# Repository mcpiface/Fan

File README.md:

# Fan

## Versions

* 1: Simple fan controlled via Raspberry Pi with 1 Wire temperature sensor.
* 2: I2C temperature sensor
* 3: I2C interface to AT Tiny 85 controller for the fan with accelerometer (internal temperature sensor).

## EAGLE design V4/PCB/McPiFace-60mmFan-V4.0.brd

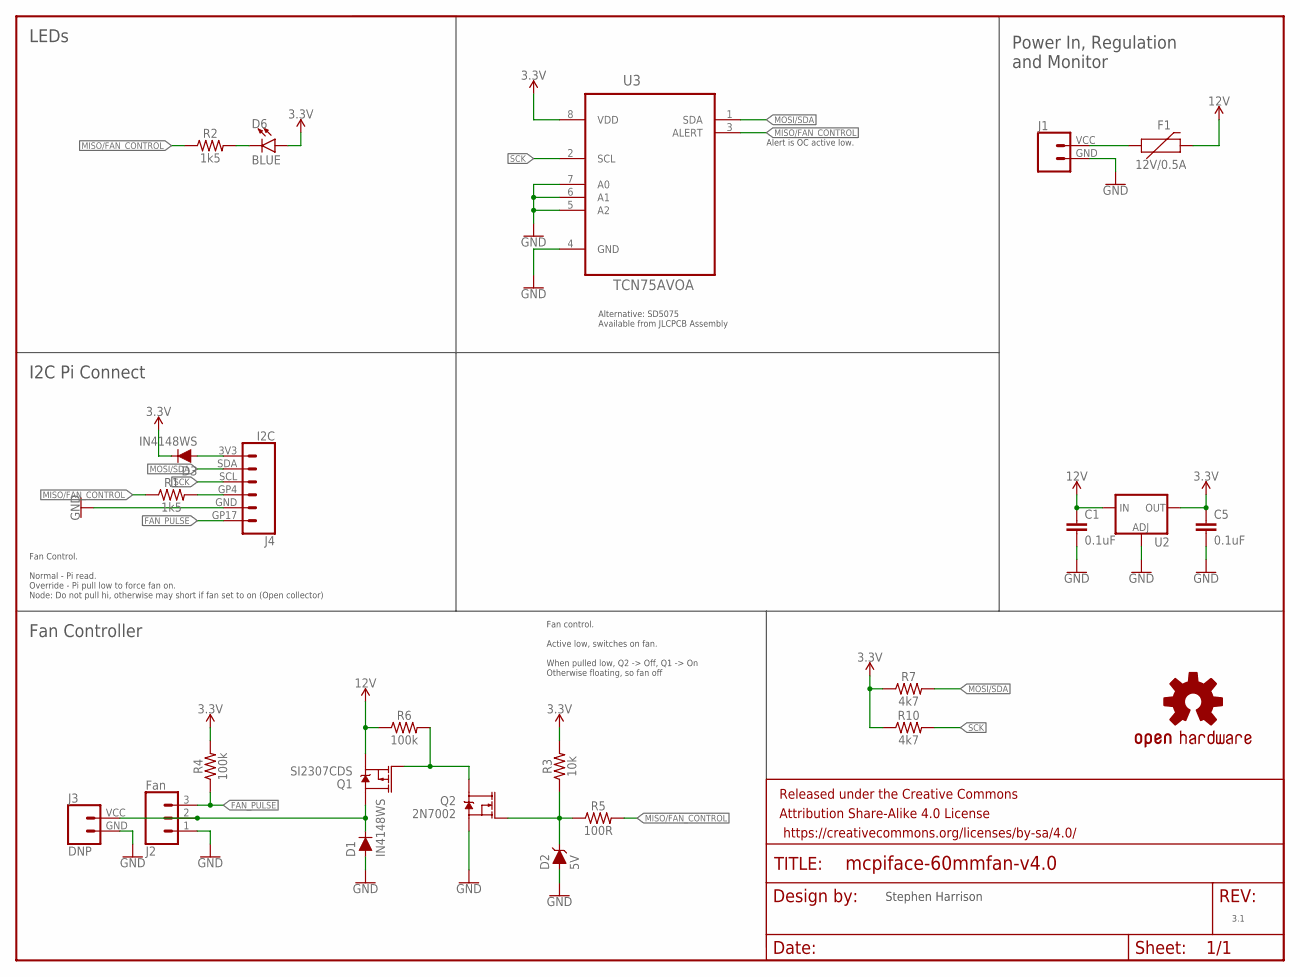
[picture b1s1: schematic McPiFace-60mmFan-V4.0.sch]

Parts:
C1, C5: 0.1uF; 0805
D1, D3: IN4148WS; SOD-323; LCSC C2128
D2: 5V; SOD-323
D6: BLUE; LED-1206
F1: 12V/0.5A; 1206
FRAME1: FRAME-LETTER; CREATIVE_COMMONS
J1: CONN_024UCON-15767; JST-2-SMD-VERT
J2: Fan; JST-3-SMD; FARNELL 9492623
J3: DNP; JST-2-SMD-VERT
J4: I2C; JST-6-SH-1.0MM-TOP
LOGO1: OSHW-LOGOL; OSHW-LOGO-L
Q1: SI2307CDS; SOT23-3; FARNELL 1779262
Q2: 2N7002; SOT23-3; FARNELL 1510761
R1, R2: 1k5; 0805
R3: 10k; 0805
R4, R6: 100k; 0805
R5: 100R; 0805
R7, R10: 4k7; 0805
U2: V_REG_LM1117SOT223; SOT223; LCSC C126027
U3: TCN75AVOA; SOIC127P600X175-8N

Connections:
3.3V: C5.1, D3.C, D6.A, R3.2, R4.2, R7.1, R10.1, U2.2 (OUT), U2.4 (OUT), U3.8 (VDD)
12V: C1.1, F1.2, Q1.2 (S), R6.1, U2.3 (IN)
FAN_PULSE: J2.3 (1), J4.GP17, R4.1
GND: C1.2, C5.2, D1.A, D2.A, J1.GND (1), J2.1 (3), J3.GND (1), J4.GND, Q2.2 (S), U2.1 (ADJ), U3.4 (GND), U3.5 (A2), U3.6 (A1), U3.7 (A0)
MISO/FAN_CONTROL: R1.1, R2.1, R5.2, U3.3 (ALERT)
MOSI/SDA: J4.SDA, R7.2, U3.1 (SDA)
unnamed: D6.C, R2.2
unnamed: J4.GP4, R1.2
unnamed: D3.A, J4.3V3
unnamed: F1.1, J1.VCC (2)
unnamed: D1.C, J2.2, J3.VCC (2), Q1.3 (D)
unnamed: Q1.1 (G), Q2.3 (D), R6.2
unnamed: D2.C, Q2.1 (G), R3.1, R5.1
SCK: J4.SCL, R10.2, U3.2 (SCL)

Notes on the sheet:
3.1
Stephen Harrison
Fan Controller
I2C Pi Connect
Power In, Regulation and Monitor
LEDs
Alert is OC active low.
Fan control. Active low, switches on fan. When pulled low, Q2 -> Off, Q1 -> On Otherwise floating, so fan off
Fan Control. Normal - Pi read. Override - Pi pull low to force fan on. Node: Do not pull hi, otherwise may short if fan set to on (Open collector)
Alternative: SD5075 Available from JLCPCB Assembly

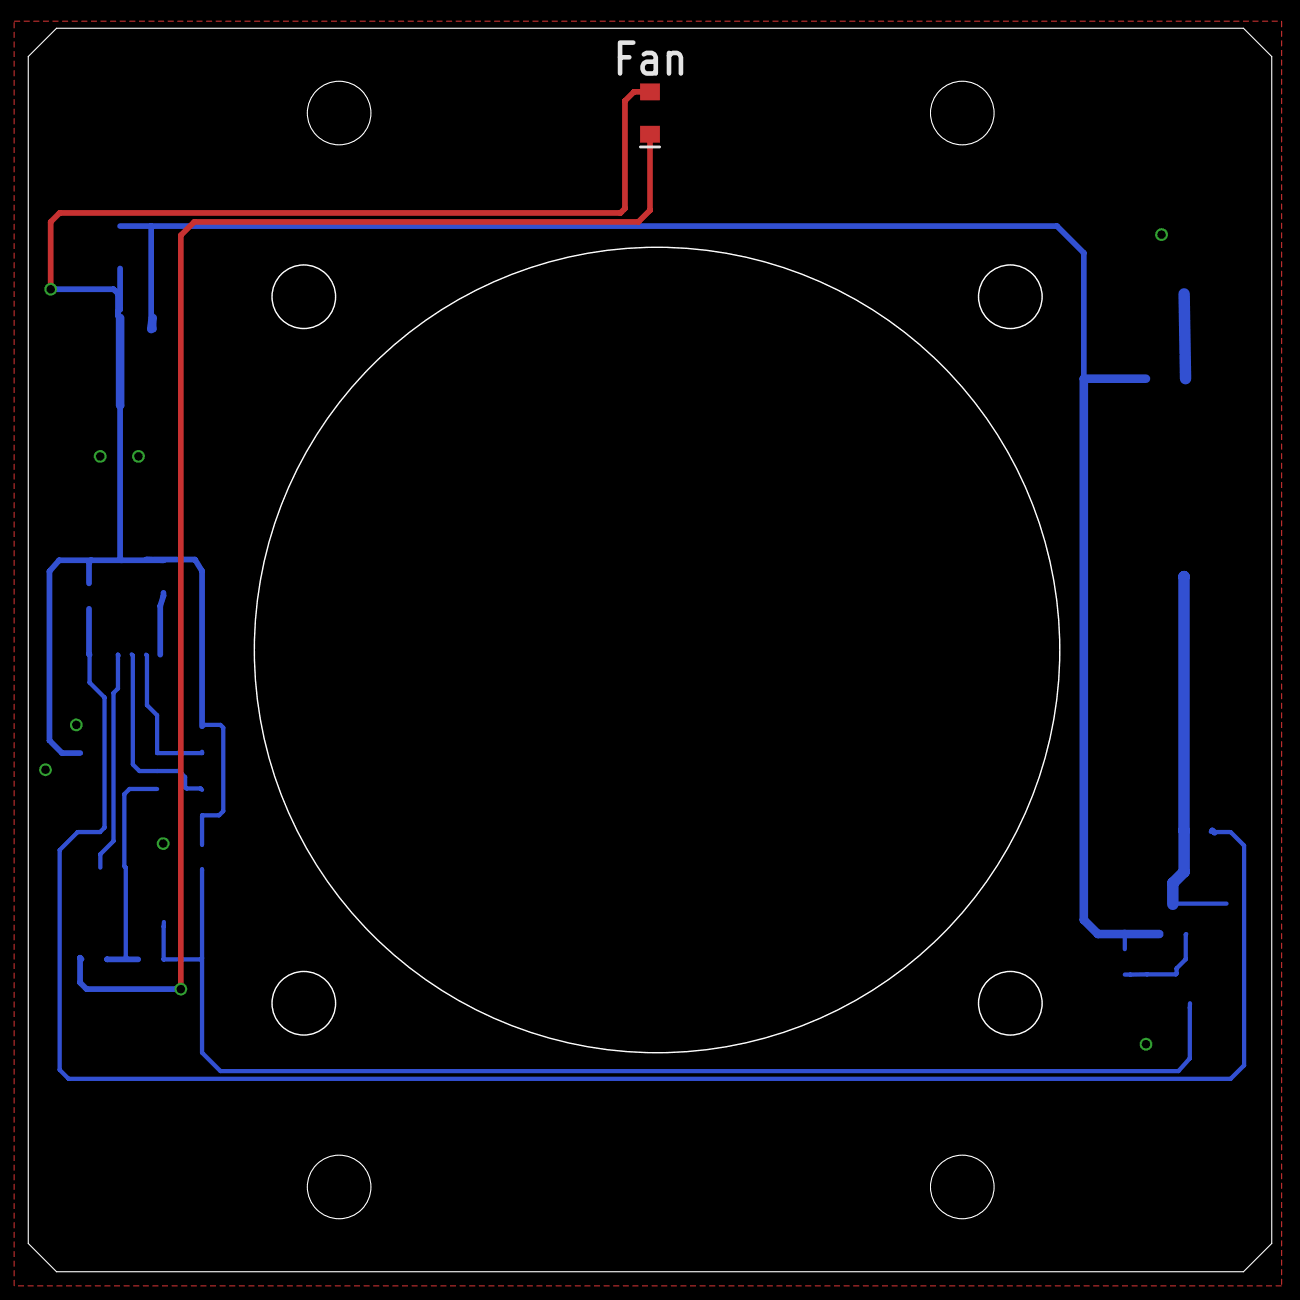
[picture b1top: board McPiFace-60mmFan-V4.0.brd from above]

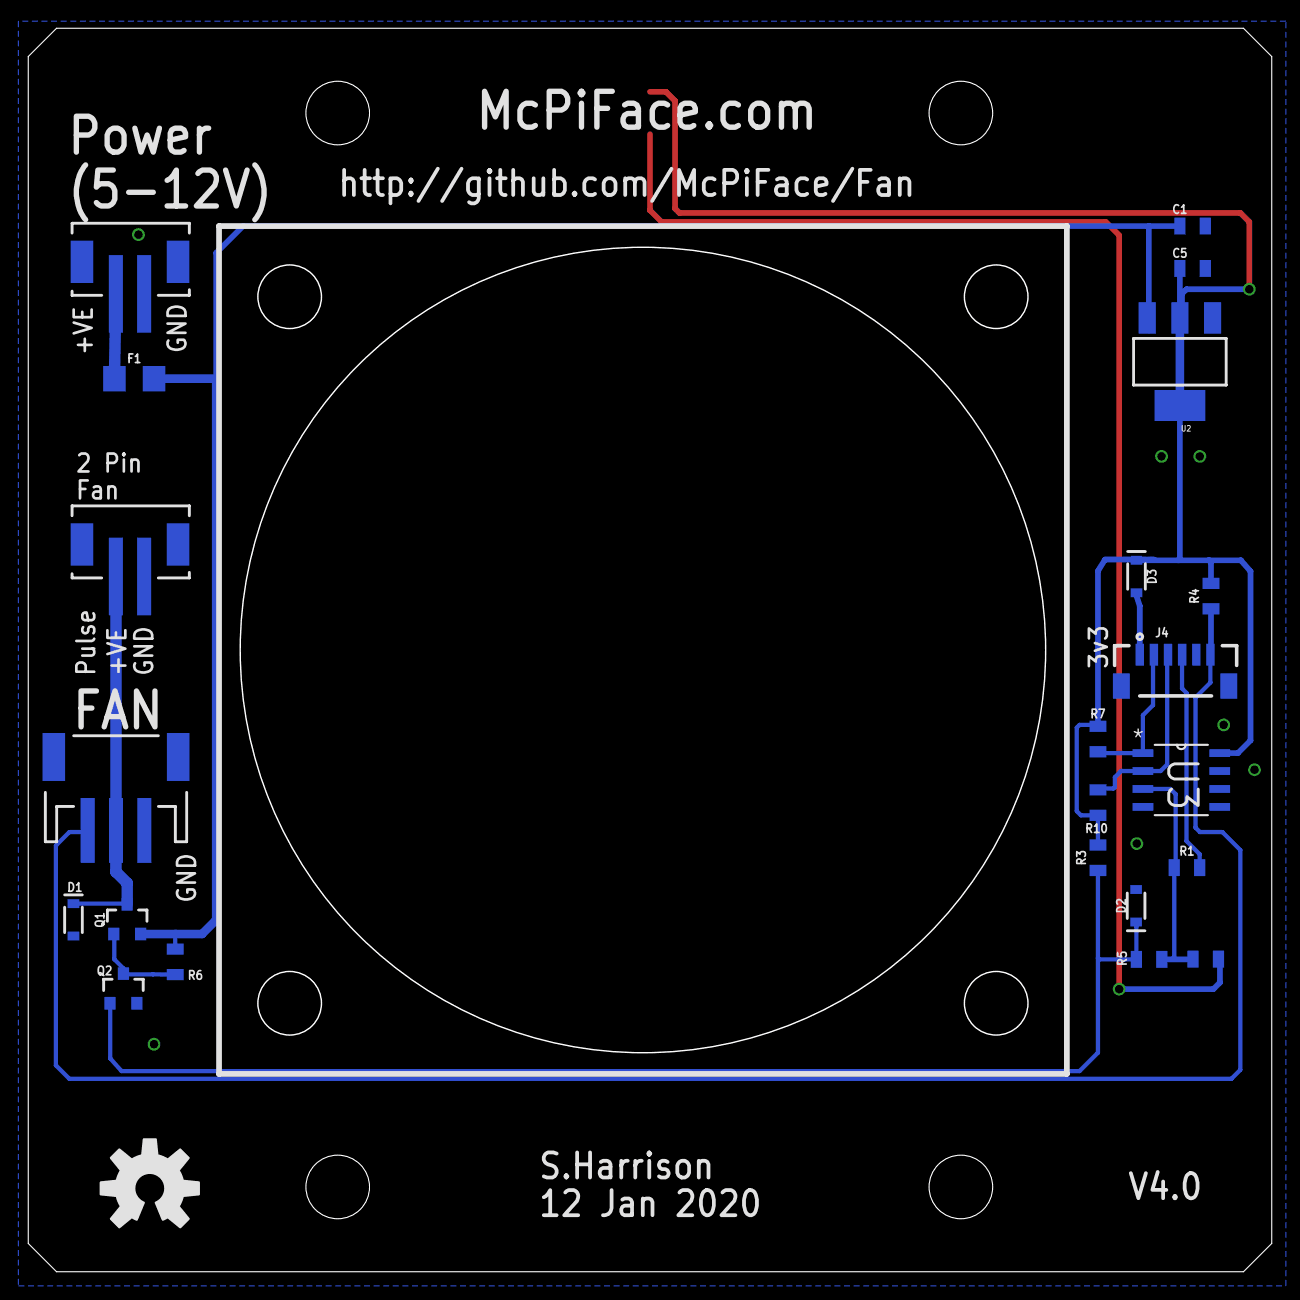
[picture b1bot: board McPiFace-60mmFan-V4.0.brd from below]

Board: 2 copper layers, 87.9 x 87.9 mm, 25 parts (23 on the bottom side), 14 nets.

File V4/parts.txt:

Partlist

Exported from McPiFace-60mmFan-V4.0.brd at 12/01/2020 14:54

EAGLE Version 7.4.0 Copyright (c) 1988-2015 CadSoft

Assembly variant: 

Part     Value          Package            Library               Position (inch)       Orientation

C1       0.1uF          0805               ThingySticks          (0.22047244 2.91338583) MR0
C5       0.1uF          0805               ThingySticks          (0.22047244 2.79527559) MR0
D1       IN4148WS       SOD-323            SparkFun-DiscreteSemi (3.33858268 0.98031496) MR270
D2       5V             SOD-323            SparkFun-DiscreteSemi (0.37795276 1.01968504) MR90
D3       IN4148WS       SOD-323            SparkFun-DiscreteSemi (0.37677165 1.93700787) MR270
D6       BLUE           LED-1206           ThingySticks          (1.73228346 3.22834646) R270
F1       12V/0.5A       1206               SparkFun-Fuses        (3.16929134 2.48818898) MR0
J1                      JST-2-SMD-VERT     SparkFun-Connectors   (3.18110236 2.80314961) MR0
J2       Fan            JST-3-SMD          SparkFun-Connectors   (3.22047244 1.41732283) MR0
J3       DNP            JST-2-SMD-VERT     SparkFun-Connectors   (3.18110236 2.01574803) MR0
J4       I2C            JST-6-SH-1.0MM-TOP McPiFace              (0.26771654 1.66929134) MR0
Q1       SI2307CDS      SOT23-3            SparkFun-DiscreteSemi (3.18897638 0.98031496) MR0
Q2       2N7002         SOT23-3            SparkFun-DiscreteSemi (3.19940945 0.78740157) MR0
R1       1k5            0805               SparkFun-Resistors    (0.23622047 1.12598425) MR0
R2       1k5            0805               SparkFun-Resistors    (0.18385827 0.87086614) MR0
R3       10k            0805               SparkFun-Resistors    (0.48425197 1.15354331) MR90
R4       100k           0805               SparkFun-Resistors    (0.16929134 1.88248031) MR90
R5       100R           0805               SparkFun-Resistors    (0.34173228 0.87027559) MR0
R6       100k           0805               SparkFun-Resistors    (3.05511811 0.86338583) MR270
R7       4k7            0805               SparkFun-Resistors    (0.48425197 1.48425197) MR270
R10      4k7            0805               SparkFun-Resistors    (0.48425197 1.30708661) MR90
U2                      SOT223             SparkFun-IC-Power     (0.25590551 2.53543307) MR180
U3       TCN75AVOA      SOIC127P600X175-8N Microchip-TCN75AVOA   (0.2519685 1.37007874) MR0

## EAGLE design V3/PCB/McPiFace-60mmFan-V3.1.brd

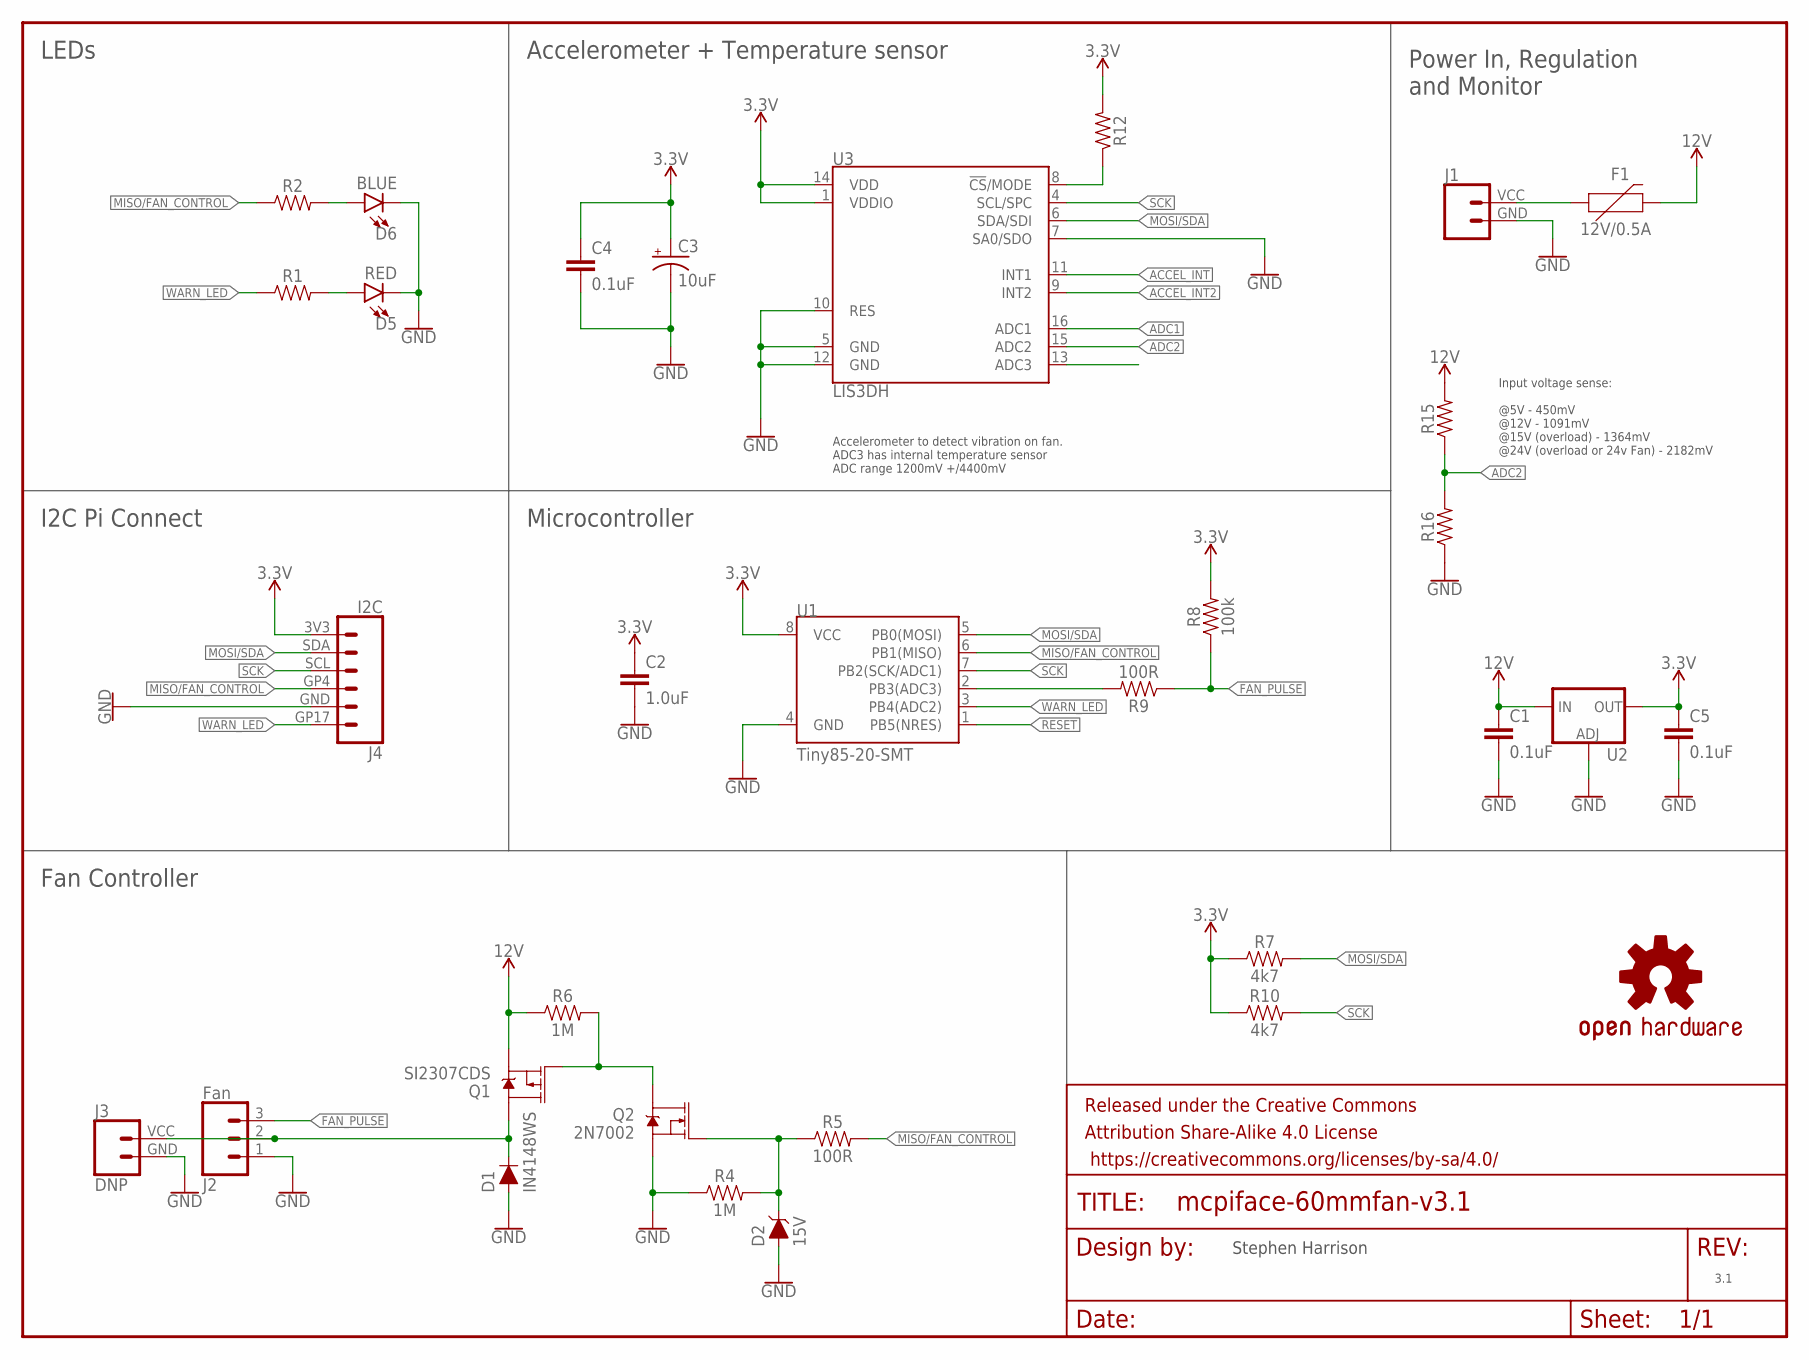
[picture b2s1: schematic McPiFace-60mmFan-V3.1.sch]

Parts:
C1, C4, C5: 0.1uF; 0805
C2: 1.0uF; 0805
C3: 10uF; EIA3216
D1: IN4148WS; SOD-323; LCSC C2128
D2: 15V; SOD-323
D5: RED; LED-1206
D6: BLUE; LED-1206
F1: 12V/0.5A; 1206
FRAME1: FRAME-LETTER; CREATIVE_COMMONS
J1: CONN_024UCON-15767; JST-2-SMD-VERT
J2: Fan; JST-3-SMD; FARNELL 9492623
J3: DNP; JST-2-SMD-VERT
J4: I2C; JST-6-SH-1.0MM-TOP
LOGO1: OSHW-LOGOL; OSHW-LOGO-L
Q1: SI2307CDS; SOT23-3; FARNELL 1779262
Q2: 2N7002; SOT23-3; FARNELL 1510761
R1, R2, R12, R15, R16: 0805
R4, R6: 1M; 0805
R5, R9: 100R; 0805
R7, R10: 4k7; 0805
R8: 100k; 0805
U1: Tiny85-20-SMT; SO08-EIAJ
U2: V_REG_LM1117SOT223; SOT223; LCSC C126027
U3: LIS3DH; LGA-16-3X3

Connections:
3.3V: C2.1, C3.A (+), C4.1, C5.1, J4.3V3, R7.1, R8.2, R10.1, R12.2, U1.8 (VCC), U2.2 (OUT), U2.4 (OUT), U3.1 (VDDIO), U3.14 (VDD)
12V: C1.1, F1.2, Q1.2 (S), R6.1, R15.2, U2.3 (IN)
ACCEL_INT: U3.11 (INT1)
ACCEL_INT2: U3.9 (INT2)
ADC1: U3.16 (ADC1)
ADC2: R15.1, R16.2, U3.15 (ADC2)
FAN_PULSE: J2.3 (1), R8.1, R9.1
GND: C1.2, C2.2, C3.C (-), C4.2, C5.2, D1.A, D2.A, D5.C, D6.C, J1.GND (1), J2.1 (3), J3.GND (1), J4.GND, Q2.2 (S), R4.1, R16.1, U1.4 (GND), U2.1 (ADJ), U3.5 (GND), U3.7 (SA0/SDO), U3.10 (RES), U3.12 (GND)
MISO/FAN_CONTROL: J4.GP4, R2.1, R5.2, U1.6 (PB1(MISO))
MOSI/SDA: J4.SDA, R7.2, U1.5 (PB0(MOSI)), U3.6 (SDA/SDI)
unnamed: R9.2, U1.2 (PB3(ADC3))
unnamed: D6.A, R2.2
unnamed: D5.A, R1.2
unnamed: F1.1, J1.VCC (2)
unnamed: R12.1, U3.8 (!CS!/MODE)
unnamed: D1.C, J2.2, J3.VCC (2), Q1.3 (D)
unnamed: Q1.1 (G), Q2.3 (D), R6.2
unnamed: D2.C, Q2.1 (G), R4.2, R5.1
RESET: U1.1 (PB5(NRES))
SCK: J4.SCL, R10.2, U1.7 (PB2(SCK/ADC1)), U3.4 (SCL/SPC)
WARN_LED: J4.GP17, R1.1, U1.3 (PB4(ADC2))

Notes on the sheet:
Accelerometer to detect vibration on fan. ADC3 has internal temperature sensor ADC range 1200mV +/4400mV
Input voltage sense: @5V - 450mV @12V - 1091mV @15V (overload) - 1364mV @24V (overload or 24v Fan) - 2182mV
3.1
Stephen Harrison
Fan Controller
I2C Pi Connect
Microcontroller
Power In, Regulation and Monitor
Accelerometer + Temperature sensor
LEDs

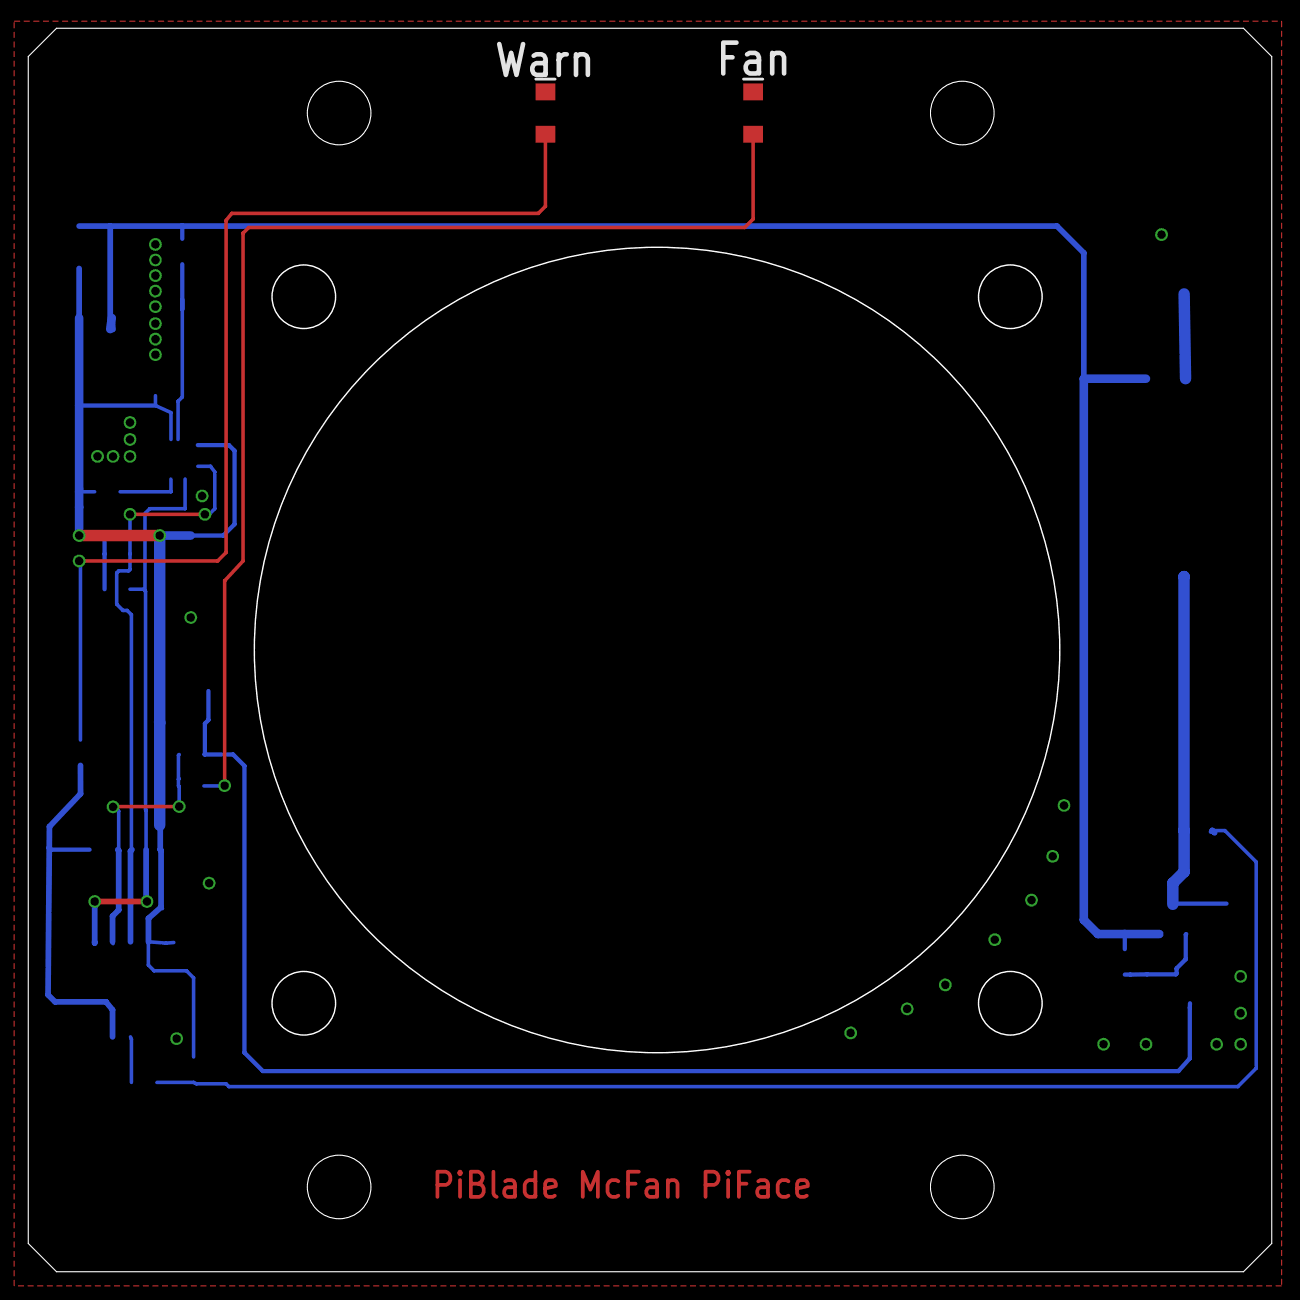
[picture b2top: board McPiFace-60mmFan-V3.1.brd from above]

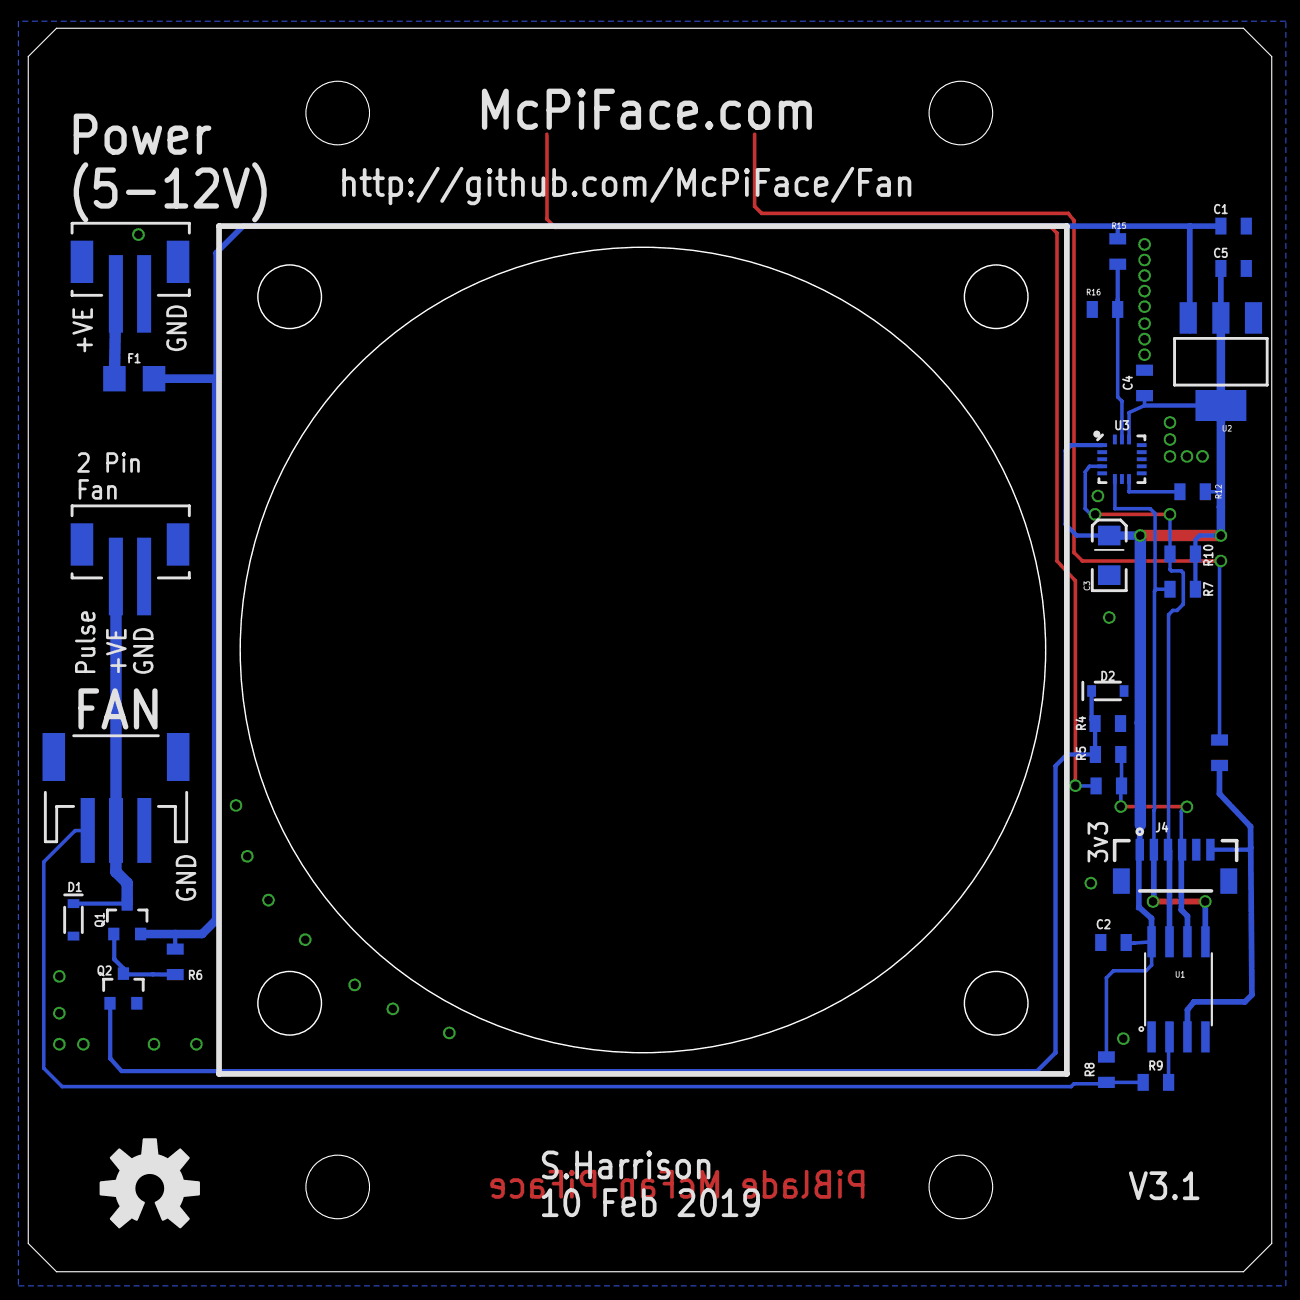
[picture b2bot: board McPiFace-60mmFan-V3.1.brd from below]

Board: 2 copper layers, 87.9 x 87.9 mm, 33 parts (30 on the bottom side), 17 nets.

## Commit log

2019-02-10 V1, 2 and 3 designs copied over from ThingySticks repository.
2019-02-10 V3.1 work in progress improvements to V3.
    Added 3v3 regulator for independant control.
    Removed AT Tiny Reset pin usage.
    Changed 6 pin connector to use McPi I2C connector pinout for 1:1 mapping to Raspberry Pi header.
    Removed OK Led. Warn and fan should be enough.
    Removed current sense resistor. Accelerometer ADC has limited range which isn't enough for current sense.
    Added optional 2 pin JST 2mm connector for fan as some fans have that already.
2020-01-12 Modified V3 to include some package details.
2020-01-12 New V4 - Using I2C temperature sensor with alarm for fan control.

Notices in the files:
parts and their libraries:
SparkFun-Aesthetics: Licensing: Creative Commons ShareAlike 4.0 International - https://creativecommons.org/licenses/by-sa/4.0
SparkFun-Aesthetics: Released under the Creative Commons Attribution Share-Alike 4.0 License
SparkFun-Aesthetics: https://creativecommons.org/licenses/by-sa/4.0
